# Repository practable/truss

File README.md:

# truss

## Introduction

The truss remote laboratory has been designed for use with Structural Engineering and Engineering Design courses at the University of Edinburgh. The truss consists of 6 members, each with a full-bridge strain gauge arrangement using two biaxial strain gauges ([Kyowa KFGS-2-120-D16-11](./hw/docs/)). Strain gauge voltages are converted to digital signals using the [HX711 ADC](./hw/docs/) and this [HX711 library](https://www.arduino.cc/reference/en/libraries/hx711-arduino-library/) is used to read and tare the gauges. The truss is loaded using a [linear servo](./hw/docs/). 

## Contents

- [Firmware ./fw](./fw/)
- [Hardware ./hw](./hw/)
- [SBC ./sbc](./sbc/)
- [UI ./ui](./ui/)

## UI

User Interfaces have been designed with Vue3.js and built with Vite. There are currently three distinct versions of the UI that are built for production:

- default: all data and components available on the user interface.
- no-force: force data is hidden for student calculation from strain data.
- open-day: simplified control interface for demonstrations.

See [here](./ui/README.md) for details of the differences.

## Changing control interface on UI

The differences in the above UI versions amount to very simple changes in the Vue files. 

The load force can be controlled with either a slider or simple buttons (as well experimental versions of a skeuomorphic display and gamepad control). Simply update the `loadControlVersion` parameter in `App.vue`.

```
loadControlVersion: 1,    //0 => input field, 1=> slider, 2=>simulation of physical knob, 3 => direct commands typed, 4 => GamePad, 5 => open day, simple buttons
```

To change whether the load force is displayed or the theoretical strains are available, update the boolean parameters in `src/modules/uiStore.js`:

```
show_force: false,       //should force values be displayed on the UI
show_theory: false,      //should the theoretical values component be available on the UI
```

## Firmware

The truss remote lab has been designed around the Arduino Nano 33 IoT. The firmware uses a state machine with 11 states, including reading, writing, taring and resetting strain gauges and moving the linear actuator. A single microcontroller performs both reading and writing of data. The state machine will remain in the READ state until a user command to change state. Upon performing that state the state machine will return to READ. The required libraries are included [here](./fw/libraries/). 

The firmware sends and receives JSON messages, eg:

Mode control, received from UI through Serial (for all commands see [SerialCommands](./fw/MiniTruss/):

```
{"set": "position", "to": value} 
{"set": "mode", "to": "move"} 
{"set": "mode", "to":"tare_all"} 
```

Sending data to UI through Serial:
```
{"load_cell":"20.0", "gauge_1": "100.0", "gauge_2": "100.0", "gauge_3": "100.0", "gauge_4": "100.0", "gauge_5": "100.0", "gauge_6": "100.0", "state":"1", "pos":"10"}
```

## PCB

The PCB requires a 12V input and provides output voltages for different components: 10V (load cell excitation voltage), 6V (linear actuator power) and 5V (strain gauge excitation voltage). Details of jumper requirements for setting up the PCB in different modes will be added (TODO).

## Hardware

The [Actuonix L16](./hw/docs/Actuonix+L16+Datasheet.pdf) linear actuator uses the custom library LinearServo for setting its position. It has a 50mm stroke length, but is limited in this remote lab to a maximum of 20% extension (providing around 150N of load on the truss).

## Re-calibration procedure

If a strain gauge value no longer reads an acceptable result (within your experimental tolerance) then the scale factor needs to be updated in the firmware.

- Note the value in micro-strain that the gauge is currently reading (current_value)
- Note the current scale factor for that gauge (current_factor)
- Calculate the value that you want it to read based on the load force (new_value)
- new_factor = current_value*current_factor / new_value

Using the debug UI (or any other means of sending a JSON command through Websocket to the experiment): send the new calibration data:

```
{"set":"cal","to":[2.0,2.1,2.2,2.3,2.4,2.5,2.6],"auth":"foo"}
```

Using the auth code that you set up initially.

Then reset to the STARTUP state so that the firmware loads the new calibration data:

```
{"set":"state","to":"STATE_STARTUP"}
```

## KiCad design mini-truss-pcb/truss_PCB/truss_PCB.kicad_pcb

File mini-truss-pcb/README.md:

## Mini Truss PCB design

# Current state

An Arduino Nano 33 IoT is used as the microcontroller for the lab. Firmware, in an unfinished state, is available [here](https://github.com/dpreid/truss-firmware/tree/main/MiniTruss). The latest mini-truss firmware is available on the develop branch.

The PCB design currently consists of the analogue-to-digital converters (ADC) for strain gauge measurements and the Arduino Nano 33 IoT. The ADC uses the [HX711](https://github.com/dpreid/mini-truss-pcb/blob/main/docs/hx711_english.pdf)

Firmware and PCB updates for the new [linear actuator](https://github.com/dpreid/mini-truss-pcb/blob/main/docs/Actuonix%2BL16%2BDatasheet.pdf) have been incorporated into the latest version.

# TODO

- Check correct resistance values are being used for voltage divider within ADC unit (R1 and R2 and then equivalents).
- TBC, whether we will stick with the Arduino Nano 33 IoT or convert to using Tim Drysdale's custom [microcontroller board](https://github.com/timdrysdale/atmega-demo). Perhaps better to use Arduino Nano (ie not 33 IoT) or Uno in order to have 5V pins and not require a logic level shifter.
- testing with prototype mini truss once strain gauges are ordered.

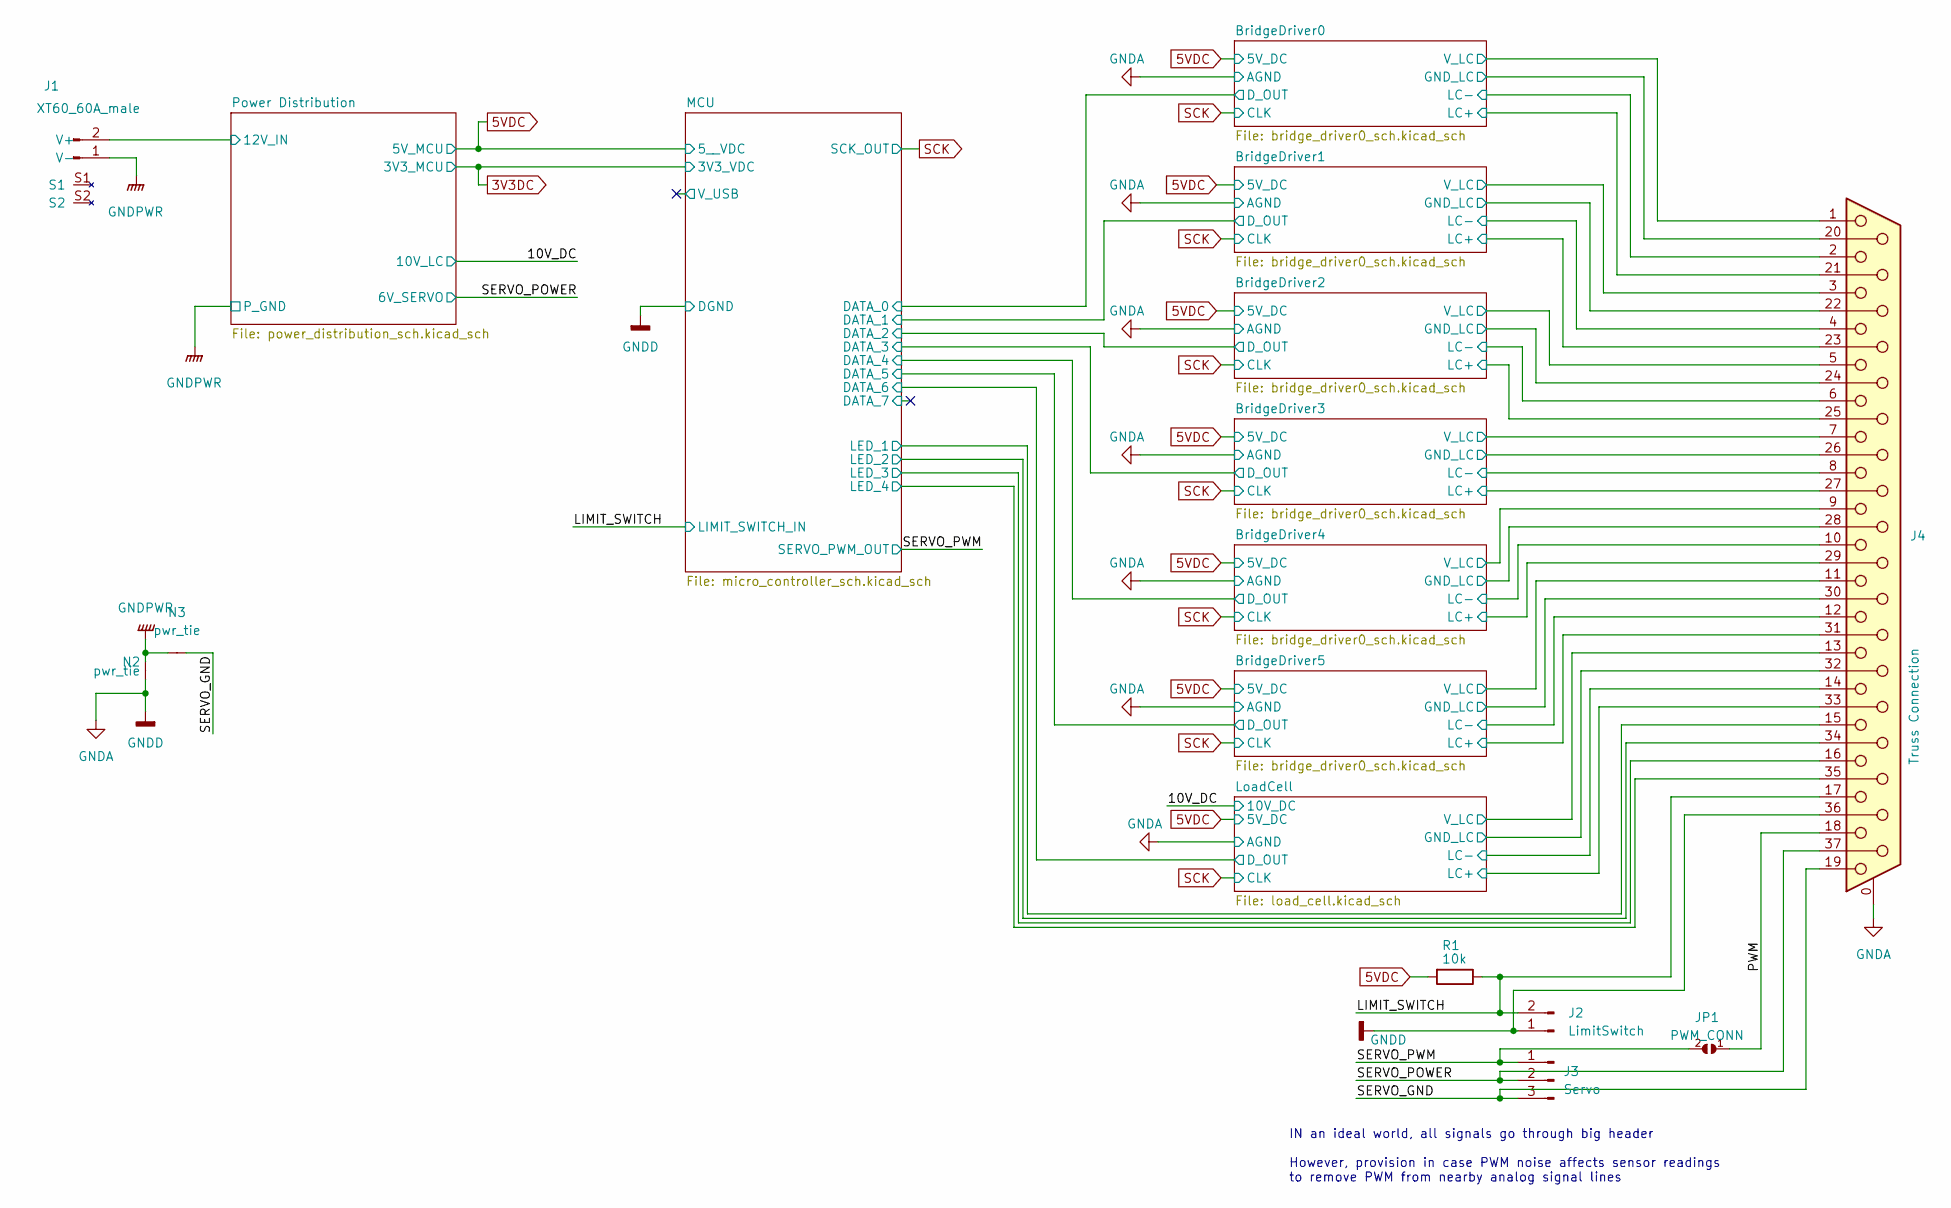
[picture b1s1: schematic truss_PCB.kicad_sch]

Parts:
J1: XT60_60A_male; AMASS_XT60PW-M
J2: LimitSwitch; Molex_KK-254_AE-6410-02A_1x02_P2.54mm_Vertical
J3: Servo; PinHeader_1x03_P2.54mm_Vertical
J4: Truss Connection; DSUB-37_Female_Vertical_P2.77x2.84mm_MountingHoles
JP1: PWM_CONN; SolderJumper-2_P1.3mm_Open_RoundedPad1.0x1.5mm
N2, N3: pwr_tie; NetTie-8-15A_1oz_2oz
R1: 10k; R_0805_2012Metric_Pad1.20x1.40mm_HandSolder

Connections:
5VDC: R1.2; also elsewhere on the board
/BridgeDriver0/LC+: J4.21; also elsewhere on the board
/BridgeDriver0/LC-: J4.2; also elsewhere on the board
/BridgeDriver0/V_LC: J4.1; also elsewhere on the board
/BridgeDriver1/LC+: J4.23; also elsewhere on the board
/BridgeDriver1/LC-: J4.4; also elsewhere on the board
/BridgeDriver1/V_LC: J4.3; also elsewhere on the board
/BridgeDriver2/LC+: J4.25; also elsewhere on the board
/BridgeDriver2/LC-: J4.6; also elsewhere on the board
/BridgeDriver2/V_LC: J4.5; also elsewhere on the board
/BridgeDriver3/LC+: J4.27; also elsewhere on the board
/BridgeDriver3/LC-: J4.8; also elsewhere on the board
/BridgeDriver3/V_LC: J4.7; also elsewhere on the board
/BridgeDriver4/LC+: J4.29; also elsewhere on the board
/BridgeDriver4/LC-: J4.10; also elsewhere on the board
/BridgeDriver4/V_LC: J4.9; also elsewhere on the board
/BridgeDriver5/LC+: J4.31; also elsewhere on the board
/BridgeDriver5/LC-: J4.12; also elsewhere on the board
/BridgeDriver5/V_LC: J4.11; also elsewhere on the board
/LIMIT_SWITCH: J2.2, J4.17, R1.1; also elsewhere on the board
/LoadCell/LC+: J4.33; also elsewhere on the board
/LoadCell/LC-: J4.14; also elsewhere on the board
/LoadCell/V_LC: J4.13; also elsewhere on the board
/MCU/LED_2: J4.34; also elsewhere on the board
/MCU/LED_3: J4.16; also elsewhere on the board
/MCU/LED_4: J4.35; also elsewhere on the board
/MCU/SPARE_0: J4.15; also elsewhere on the board
/PWM: J4.18, JP1.1 (A)
/Power Distribution/12V_IN: J1.2 (V+); also elsewhere on the board
/SERVO_GND: J3.3, J4.19, N3.2 (C)
/SERVO_POWER: J3.2, J4.37; also elsewhere on the board
/SERVO_PWM: J3.1, JP1.2 (B); also elsewhere on the board
GNDA: J2.1, J4.0 (PAD), J4.20, J4.22, J4.24, J4.26, J4.28, J4.30, J4.32, J4.36, N2.1 (A); also elsewhere on the board
GNDPWR: J1.1 (V-), N2.2 (C), N3.1 (A); also elsewhere on the board

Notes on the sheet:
IN an ideal world, all signals go through big header However, provision in case PWM noise affects sensor readings to remove PWM from nearby analog signal lines

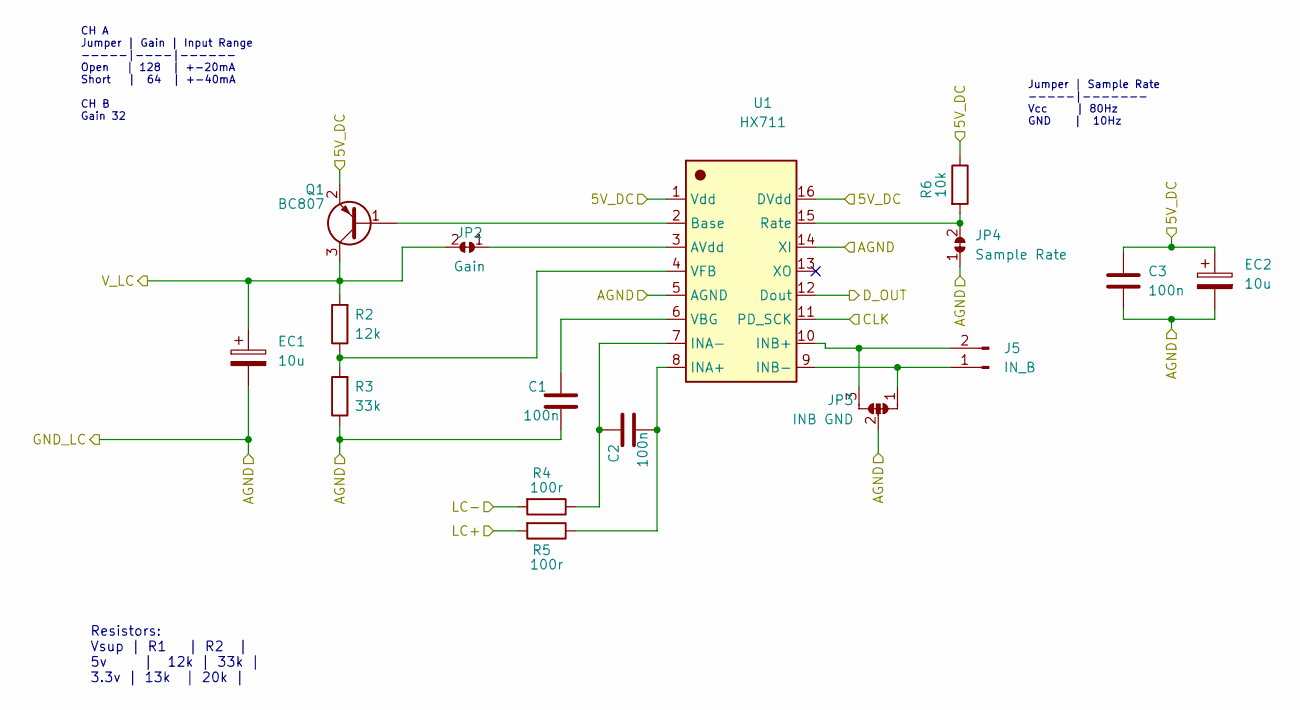
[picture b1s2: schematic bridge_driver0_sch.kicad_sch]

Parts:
C1, C2, C3: 100n; C_0805_2012Metric_Pad1.18x1.45mm_HandSolder
EC1, EC2: 10u; CP_Elec_6.3x5.9
J5: IN_B; PinHeader_1x02_P1.27mm_Vertical
JP2: Gain; SolderJumper-2_P1.3mm_Bridged_RoundedPad1.0x1.5mm
JP3: INB GND; SolderJumper-3_P1.3mm_Bridged12_RoundedPad1.0x1.5mm_DoubleJ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
JP4: Sample Rate; SolderJumper-2_P1.3mm_Bridged_RoundedPad1.0x1.5mm
Q1: BC807; SOT-23
R2: 12k; R_0805_2012Metric_Pad1.20x1.40mm_HandSolder
R3: 33k; R_0805_2012Metric_Pad1.20x1.40mm_HandSolder
R4, R5: 100r; R_0805_2012Metric_Pad1.20x1.40mm_HandSolder
R6: 10k; R_0805_2012Metric_Pad1.20x1.40mm_HandSolder
U1: HX711; SOP-16_4.55x10.3mm_P1.27mm

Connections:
5VDC: C3.1, EC2.1, Q1.2 (E), R6.1, U1.1 (Vdd), U1.16 (DVdd); also elsewhere on the board
/BridgeDriver0/D_OUT: U1.12 (Dout); also elsewhere on the board
/BridgeDriver0/LC+: R5.2; also elsewhere on the board
/BridgeDriver0/LC-: R4.2; also elsewhere on the board
/BridgeDriver0/V_LC: EC1.1, JP2.2 (B), Q1.3 (C), R2.2; also elsewhere on the board
GNDA: C1.2, C3.2, EC1.2, EC2.2, JP3.2 (C), JP4.1 (A), R3.1, U1.5 (AGND), U1.14 (XI); also elsewhere on the board
unnamed: C1.1, U1.6 (VBG)
unnamed: C2.1, R4.1, U1.7 (INA-)
unnamed: C2.2, R5.1, U1.8 (INA+)
unnamed: J5.1, JP3.1 (A), U1.9 (INB-)
unnamed: J5.2, JP3.3 (B), U1.10 (INB+)
unnamed: JP2.1 (A), U1.3 (AVdd)
unnamed: JP4.2 (B), R6.2, U1.15 (Rate)
unnamed: Q1.1 (B), U1.2 (Base)
unnamed: R2.1, R3.2, U1.4 (VFB)
SCK: U1.11 (PD_SCK); also elsewhere on the board

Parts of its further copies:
C4, C5, C6, C7, C8, C9, C10, C11, C12, C13, C14, C15, C16, C17, C18: 100n; C_0805_2012Metric_Pad1.18x1.45mm_HandSolder
EC3, EC4, EC5, EC6, EC7, EC8, EC9, EC10, EC11, EC12: 10u; CP_Elec_6.3x5.9
J6, J7, J8, J9, J10: IN_B; PinHeader_1x02_P1.27mm_Vertical
JP5, JP8, JP11, JP14, JP17: Gain; SolderJumper-2_P1.3mm_Bridged_RoundedPad1.0x1.5mm
JP6, JP9, JP12, JP15, JP18: INB GND; SolderJumper-3_P1.3mm_Bridged12_RoundedPad1.0x1.5mm_DoubleJ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
JP7, JP10, JP13, JP16, JP19: Sample Rate; SolderJumper-2_P1.3mm_Bridged_RoundedPad1.0x1.5mm
Q2, Q3, Q4, Q5, Q6: BC807; SOT-23
R7, R12, R17, R22, R27: 12k; R_0805_2012Metric_Pad1.20x1.40mm_HandSolder
R8, R13, R18, R23, R28: 33k; R_0805_2012Metric_Pad1.20x1.40mm_HandSolder
R9, R10, R14, R15, R19, R20, R24, R25, R29, R30: 100r; R_0805_2012Metric_Pad1.20x1.40mm_HandSolder
R11, R16, R21, R26, R31: 10k; R_0805_2012Metric_Pad1.20x1.40mm_HandSolder
U2, U3, U4, U5, U6: HX711; SOP-16_4.55x10.3mm_P1.27mm

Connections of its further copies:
5VDC: C6.1, C9.1, C12.1, C15.1, C18.1, EC4.1, EC6.1, EC8.1, EC10.1, EC12.1, Q2.2 (E), Q3.2 (E), Q4.2 (E), Q5.2 (E), Q6.2 (E), R11.1, R16.1, R21.1, R26.1, R31.1, U2.1 (Vdd), U2.16 (DVdd), U3.1 (Vdd), U3.16 (DVdd), U4.1 (Vdd), U4.16 (DVdd), U5.1 (Vdd), U5.16 (DVdd), U6.1 (Vdd), U6.16 (DVdd); also elsewhere on the board
/BridgeDriver1/D_OUT: U2.12 (Dout); also elsewhere on the board
/BridgeDriver1/LC+: R10.2; also elsewhere on the board
/BridgeDriver1/LC-: R9.2; also elsewhere on the board
/BridgeDriver1/V_LC: EC3.1, JP5.2 (B), Q2.3 (C), R7.2; also elsewhere on the board
/BridgeDriver2/D_OUT: U3.12 (Dout); also elsewhere on the board
/BridgeDriver2/LC+: R15.2; also elsewhere on the board
/BridgeDriver2/LC-: R14.2; also elsewhere on the board
/BridgeDriver2/V_LC: EC5.1, JP8.2 (B), Q3.3 (C), R12.2; also elsewhere on the board
/BridgeDriver3/D_OUT: U4.12 (Dout); also elsewhere on the board
/BridgeDriver3/LC+: R20.2; also elsewhere on the board
/BridgeDriver3/LC-: R19.2; also elsewhere on the board
/BridgeDriver3/V_LC: EC7.1, JP11.2 (B), Q4.3 (C), R17.2; also elsewhere on the board
/BridgeDriver4/D_OUT: U5.12 (Dout); also elsewhere on the board
/BridgeDriver4/LC+: R25.2; also elsewhere on the board
/BridgeDriver4/LC-: R24.2; also elsewhere on the board
/BridgeDriver4/V_LC: EC9.1, JP14.2 (B), Q5.3 (C), R22.2; also elsewhere on the board
/BridgeDriver5/D_OUT: U6.12 (Dout); also elsewhere on the board
/BridgeDriver5/LC+: R30.2; also elsewhere on the board
/BridgeDriver5/LC-: R29.2; also elsewhere on the board
/BridgeDriver5/V_LC: EC11.1, JP17.2 (B), Q6.3 (C), R27.2; also elsewhere on the board
GNDA: C4.2, C6.2, C7.2, C9.2, C10.2, C12.2, C13.2, C15.2, C16.2, C18.2, EC3.2, EC4.2, EC5.2, EC6.2, EC7.2, EC8.2, EC9.2, EC10.2, EC11.2, EC12.2, JP6.2 (C), JP7.1 (A), JP9.2 (C), JP10.1 (A), JP12.2 (C), JP13.1 (A), JP15.2 (C), JP16.1 (A), JP18.2 (C), JP19.1 (A), R8.1, R13.1, R18.1, R23.1, R28.1, U2.5 (AGND), U2.14 (XI), U3.5 (AGND), U3.14 (XI), U4.5 (AGND), U4.14 (XI), U5.5 (AGND), U5.14 (XI), U6.5 (AGND), U6.14 (XI); also elsewhere on the board
unnamed: C4.1, U2.6 (VBG)
unnamed: C5.1, R9.1, U2.7 (INA-)
unnamed: C5.2, R10.1, U2.8 (INA+)
unnamed: C7.1, U3.6 (VBG)
unnamed: C8.1, R14.1, U3.7 (INA-)
unnamed: C8.2, R15.1, U3.8 (INA+)
unnamed: C10.1, U4.6 (VBG)
unnamed: C11.1, R19.1, U4.7 (INA-)
unnamed: C11.2, R20.1, U4.8 (INA+)
unnamed: C13.1, U5.6 (VBG)
unnamed: C14.1, R24.1, U5.7 (INA-)
unnamed: C14.2, R25.1, U5.8 (INA+)
unnamed: C16.1, U6.6 (VBG)
unnamed: C17.1, R29.1, U6.7 (INA-)
unnamed: C17.2, R30.1, U6.8 (INA+)
unnamed: J6.1, JP6.1 (A), U2.9 (INB-)
unnamed: J6.2, JP6.3 (B), U2.10 (INB+)
unnamed: J7.1, JP9.1 (A), U3.9 (INB-)
unnamed: J7.2, JP9.3 (B), U3.10 (INB+)
unnamed: J8.1, JP12.1 (A), U4.9 (INB-)
unnamed: J8.2, JP12.3 (B), U4.10 (INB+)
unnamed: J9.1, JP15.1 (A), U5.9 (INB-)
unnamed: J9.2, JP15.3 (B), U5.10 (INB+)
unnamed: J10.1, JP18.1 (A), U6.9 (INB-)
unnamed: J10.2, JP18.3 (B), U6.10 (INB+)
unnamed: JP5.1 (A), U2.3 (AVdd)
unnamed: JP7.2 (B), R11.2, U2.15 (Rate)
unnamed: JP8.1 (A), U3.3 (AVdd)
unnamed: JP10.2 (B), R16.2, U3.15 (Rate)
unnamed: JP11.1 (A), U4.3 (AVdd)
unnamed: JP13.2 (B), R21.2, U4.15 (Rate)
unnamed: JP14.1 (A), U5.3 (AVdd)
unnamed: JP16.2 (B), R26.2, U5.15 (Rate)
unnamed: JP17.1 (A), U6.3 (AVdd)
unnamed: JP19.2 (B), R31.2, U6.15 (Rate)
unnamed: Q2.1 (B), U2.2 (Base)
unnamed: Q3.1 (B), U3.2 (Base)
unnamed: Q4.1 (B), U4.2 (Base)
unnamed: Q5.1 (B), U5.2 (Base)
unnamed: Q6.1 (B), U6.2 (Base)
unnamed: R7.1, R8.2, U2.4 (VFB)
unnamed: R12.1, R13.2, U3.4 (VFB)
unnamed: R17.1, R18.2, U4.4 (VFB)
unnamed: R22.1, R23.2, U5.4 (VFB)
unnamed: R27.1, R28.2, U6.4 (VFB)
SCK: U2.11 (PD_SCK), U3.11 (PD_SCK), U4.11 (PD_SCK), U5.11 (PD_SCK), U6.11 (PD_SCK); also elsewhere on the board

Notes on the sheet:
CH A Jumper | Gain | Input Range -----|----|------ Open | 128 | +-20mA Short | 64 | +-40mA CH B Gain 32
Resistors: Vsup | R1 | R2 | 5v | 12k | 33k | 3.3v | 13k | 20k |
Jumper | Sample Rate -----|------- Vcc | 80Hz GND | 10Hz

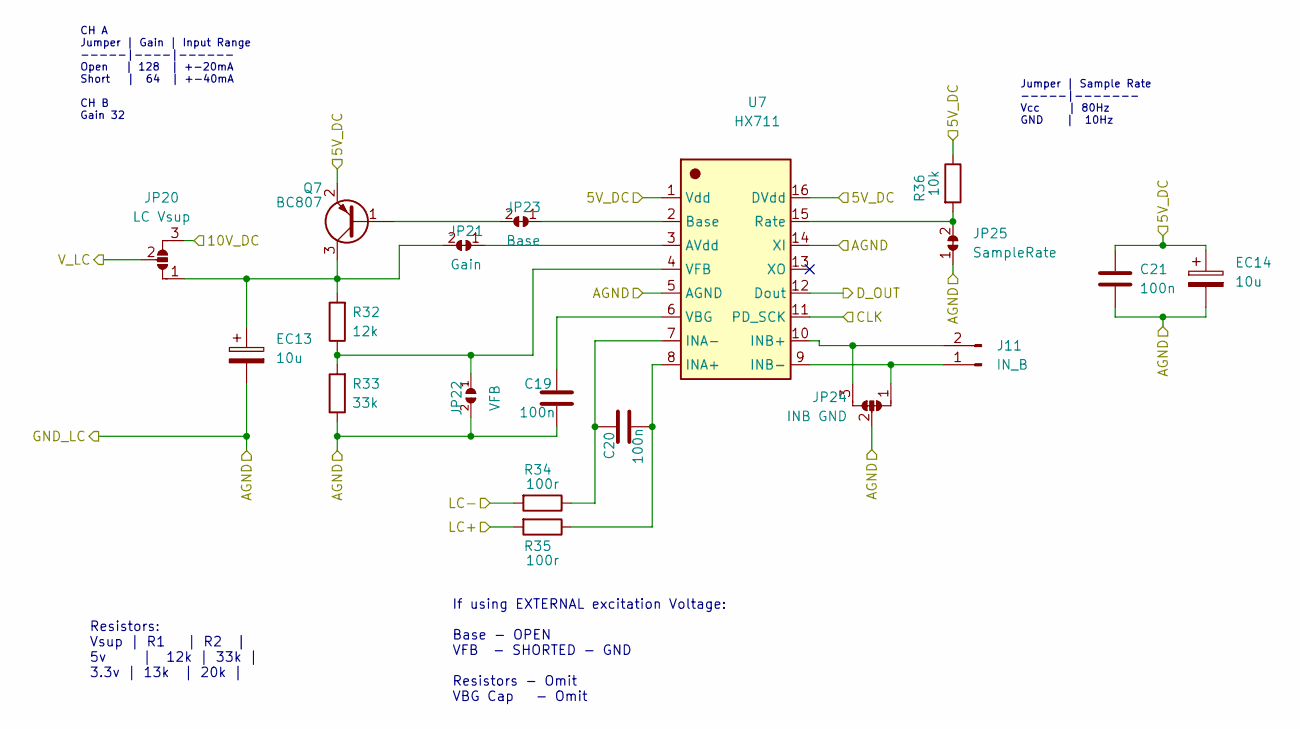
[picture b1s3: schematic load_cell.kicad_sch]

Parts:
C19, C20, C21: 100n; C_0805_2012Metric_Pad1.18x1.45mm_HandSolder
EC13, EC14: 10u; CP_Elec_6.3x5.9
J11: IN_B; PinHeader_1x02_P1.27mm_Vertical
JP20: LC Vsup; SolderJumper-3_P1.3mm_Open_RoundedPad1.0x1.5mm_NumberLabels
JP21: Gain; SolderJumper-2_P1.3mm_Bridged_RoundedPad1.0x1.5mm
JP22: VFB; SolderJumper-2_P1.3mm_Open_RoundedPad1.0x1.5mm
JP23: Base; SolderJumper-2_P1.3mm_Bridged_RoundedPad1.0x1.5mm
JP24: INB GND; SolderJumper-3_P1.3mm_Bridged12_RoundedPad1.0x1.5mm_DoubleJ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
JP25: SampleRate; SolderJumper-2_P1.3mm_Bridged_RoundedPad1.0x1.5mm
Q7: BC807; SOT-23
R32: 12k; R_0805_2012Metric_Pad1.20x1.40mm_HandSolder
R33: 33k; R_0805_2012Metric_Pad1.20x1.40mm_HandSolder
R34, R35: 100r; R_0805_2012Metric_Pad1.20x1.40mm_HandSolder
R36: 10k; R_0805_2012Metric_Pad1.20x1.40mm_HandSolder
U7: HX711; SOP-16_4.55x10.3mm_P1.27mm

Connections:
5VDC: C21.1, EC14.1, Q7.2 (E), R36.1, U7.1 (Vdd), U7.16 (DVdd); also elsewhere on the board
/10V_DC: JP20.3 (B); also elsewhere on the board
/LoadCell/D_OUT: U7.12 (Dout); also elsewhere on the board
/LoadCell/LC+: R35.2; also elsewhere on the board
/LoadCell/LC-: R34.2; also elsewhere on the board
/LoadCell/V_LC: JP20.2 (C); also elsewhere on the board
GNDA: C19.2, C21.2, EC13.2, EC14.2, JP22.2 (B), JP24.2 (C), JP25.1 (A), R33.1, U7.5 (AGND), U7.14 (XI); also elsewhere on the board
unnamed: C19.1, U7.6 (VBG)
unnamed: C20.1, R34.1, U7.7 (INA-)
unnamed: C20.2, R35.1, U7.8 (INA+)
unnamed: EC13.1, JP20.1 (A), JP21.2 (B), Q7.3 (C), R32.2
unnamed: J11.1, JP24.1 (A), U7.9 (INB-)
unnamed: J11.2, JP24.3 (B), U7.10 (INB+)
unnamed: JP21.1 (A), U7.3 (AVdd)
unnamed: JP22.1 (A), R32.1, R33.2, U7.4 (VFB)
unnamed: JP23.1 (A), U7.2 (Base)
unnamed: JP23.2 (B), Q7.1 (B)
unnamed: JP25.2 (B), R36.2, U7.15 (Rate)
SCK: U7.11 (PD_SCK); also elsewhere on the board

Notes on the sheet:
If using EXTERNAL excitation Voltage: Base - OPEN VFB - SHORTED - GND Resistors - Omit VBG Cap - Omit
Jumper | Sample Rate -----|------- Vcc | 80Hz GND | 10Hz
CH A Jumper | Gain | Input Range -----|----|------ Open | 128 | +-20mA Short | 64 | +-40mA CH B Gain 32
Resistors: Vsup | R1 | R2 | 5v | 12k | 33k | 3.3v | 13k | 20k |

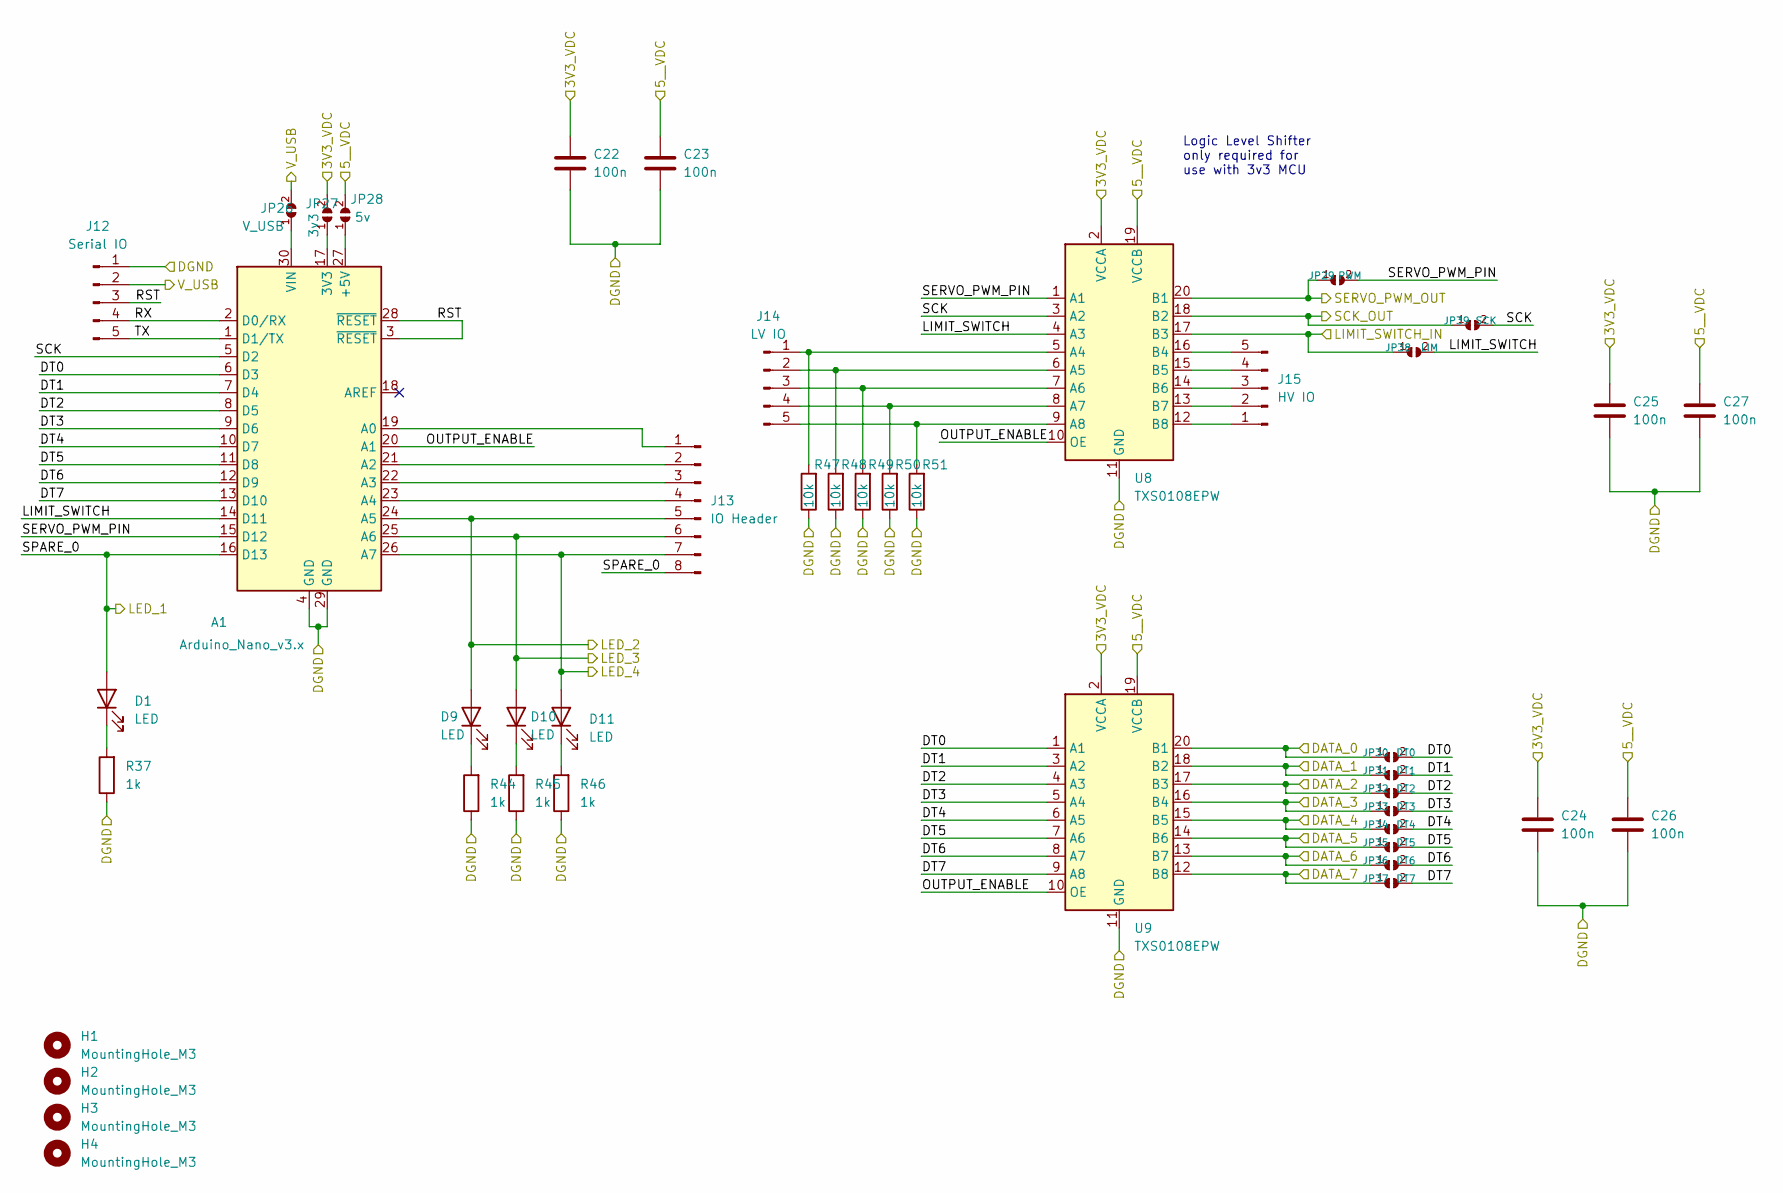
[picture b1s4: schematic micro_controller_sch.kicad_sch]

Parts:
A1: Arduino_Nano_v3.x; Arduino_Nano
C22, C23, C24, C25, C26, C27: 100n; C_0805_2012Metric_Pad1.18x1.45mm_HandSolder
D1, D9, D10, D11: LED; D_0805_2012Metric_Pad1.15x1.40mm_HandSolder
H1, H2, H3, H4: MountingHole_M3; MountingHole_3.2mm_M3_Pad_Via
J12: Serial IO; PinHeader_1x05_P2.54mm_Vertical
J13: IO Header; PinHeader_1x08_P2.54mm_Vertical
J14: LV IO; PinHeader_1x05_P2.54mm_Vertical
J15: HV IO; PinHeader_1x05_P2.54mm_Vertical
JP26: V_USB; SolderJumper-2_P1.3mm_Open_RoundedPad1.0x1.5mm
JP27: 3v3; SolderJumper-2_P1.3mm_Open_RoundedPad1.0x1.5mm
JP28: 5v; SolderJumper-2_P1.3mm_Open_RoundedPad1.0x1.5mm
JP29: PWM; SolderJumper-2_P1.3mm_Open_RoundedPad1.0x1.5mm
JP30: DT0; SolderJumper-2_P1.3mm_Open_RoundedPad1.0x1.5mm
JP31: DT1; SolderJumper-2_P1.3mm_Open_RoundedPad1.0x1.5mm
JP32: DT2; SolderJumper-2_P1.3mm_Open_RoundedPad1.0x1.5mm
JP33: DT3; SolderJumper-2_P1.3mm_Open_RoundedPad1.0x1.5mm
JP34: DT4; SolderJumper-2_P1.3mm_Open_RoundedPad1.0x1.5mm
JP35: DT5; SolderJumper-2_P1.3mm_Open_RoundedPad1.0x1.5mm
JP36: DT6; SolderJumper-2_P1.3mm_Open_RoundedPad1.0x1.5mm
JP37: DT7; SolderJumper-2_P1.3mm_Open_RoundedPad1.0x1.5mm
JP38: LIM; SolderJumper-2_P1.3mm_Open_RoundedPad1.0x1.5mm
JP39: SCK; SolderJumper-2_P1.3mm_Open_RoundedPad1.0x1.5mm
R37, R44, R45, R46: 1k; R_0805_2012Metric_Pad1.20x1.40mm_HandSolder
R47, R48, R49, R50, R51: 10k; R_0805_2012Metric_Pad1.20x1.40mm_HandSolder
U8, U9: TXS0108EPW; TSSOP-20_4.4x6.5mm_P0.65mm

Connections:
3V3DC: C22.1, C24.1, C25.1, JP27.2 (B), U8.2 (VCCA), U9.2 (VCCA); also elsewhere on the board
5VDC: C23.1, C26.1, C27.1, JP28.2 (B), U8.19 (VCCB), U9.19 (VCCB); also elsewhere on the board
/BridgeDriver0/D_OUT: JP30.1 (A), U9.20 (B1); also elsewhere on the board
/BridgeDriver1/D_OUT: JP31.1 (A), U9.18 (B2); also elsewhere on the board
/BridgeDriver2/D_OUT: JP32.1 (A), U9.17 (B3); also elsewhere on the board
/BridgeDriver3/D_OUT: JP33.1 (A), U9.16 (B4); also elsewhere on the board
/BridgeDriver4/D_OUT: JP34.1 (A), U9.15 (B5); also elsewhere on the board
/BridgeDriver5/D_OUT: JP35.1 (A), U9.14 (B6); also elsewhere on the board
/LIMIT_SWITCH: JP38.1 (A), U8.17 (B3); also elsewhere on the board
/LoadCell/D_OUT: JP36.1 (A), U9.13 (B7); also elsewhere on the board
/MCU/DATA_7: JP37.1 (A), U9.12 (B8)
/MCU/DT0: A1.6 (D3), JP30.2 (B), U9.1 (A1)
/MCU/DT1: A1.7 (D4), JP31.2 (B), U9.3 (A2)
/MCU/DT2: A1.8 (D5), JP32.2 (B), U9.4 (A3)
/MCU/DT3: A1.9 (D6), JP33.2 (B), U9.5 (A4)
/MCU/DT4: A1.10 (D7), JP34.2 (B), U9.6 (A5)
/MCU/DT5: A1.11 (D8), JP35.2 (B), U9.7 (A6)
/MCU/DT6: A1.12 (D9), JP36.2 (B), U9.8 (A7)
/MCU/DT7: A1.13 (D10), JP37.2 (B), U9.9 (A8)
/MCU/LED_2: A1.24 (A5), D9.2 (A), J13.5; also elsewhere on the board
/MCU/LED_3: A1.25 (A6), D10.2 (A), J13.6; also elsewhere on the board
/MCU/LED_4: A1.26 (A7), D11.2 (A), J13.7; also elsewhere on the board
/MCU/LIMIT_SWITCH: A1.14 (D11), JP38.2 (B), U8.4 (A3)
/MCU/OUTPUT_ENABLE: A1.20 (A1), U8.10 (OE), U9.10 (OE)
/MCU/RST: A1.3 (~RESET), A1.28 (~RESET), J12.3
/MCU/RX: A1.2 (D0/RX), J12.4
/MCU/SCK: A1.5 (D2), JP39.2 (B), U8.3 (A2)
/MCU/SERVO_PWM_PIN: A1.15 (D12), JP29.2 (B), U8.1 (A1)
/MCU/SPARE_0: A1.16 (D13), D1.2 (A), J13.8; also elsewhere on the board
/MCU/TX: A1.1 (D1/TX), J12.5
/MCU/V_USB: J12.2, JP26.2 (B)
/SERVO_PWM: JP29.1 (A), U8.20 (B1); also elsewhere on the board
GNDA: A1.4 (GND), A1.29 (GND), C22.2, C23.2, C24.2, C25.2, C26.2, C27.2, J12.1, R37.1, R44.1, R45.1, R46.1, R47.1, R48.1, R49.1, R50.1, R51.1, U8.11 (GND), U9.11 (GND); also elsewhere on the board
unnamed: A1.17 (3V3), JP27.1 (A)
unnamed: A1.19 (A0), J13.1
unnamed: A1.21 (A2), J13.2
unnamed: A1.22 (A3), J13.3
unnamed: A1.23 (A4), J13.4
unnamed: A1.27 (+5V), JP28.1 (A)
unnamed: A1.30 (VIN), JP26.1 (A)
unnamed: D1.1 (K), R37.2
unnamed: D9.1 (K), R44.2
unnamed: D10.1 (K), R45.2
unnamed: D11.1 (K), R46.2
unnamed: J14.1, R47.2, U8.5 (A4)
unnamed: J14.2, R48.2, U8.6 (A5)
unnamed: J14.3, R49.2, U8.7 (A6)
unnamed: J14.4, R50.2, U8.8 (A7)
unnamed: J14.5, R51.2, U8.9 (A8)
unnamed: J15.1, U8.12 (B8)
unnamed: J15.2, U8.13 (B7)
unnamed: J15.3, U8.14 (B6)
unnamed: J15.4, U8.15 (B5)
unnamed: J15.5, U8.16 (B4)
SCK: JP39.1 (A), U8.18 (B2); also elsewhere on the board

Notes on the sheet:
Logic Level Shifter only required for use with 3v3 MCU

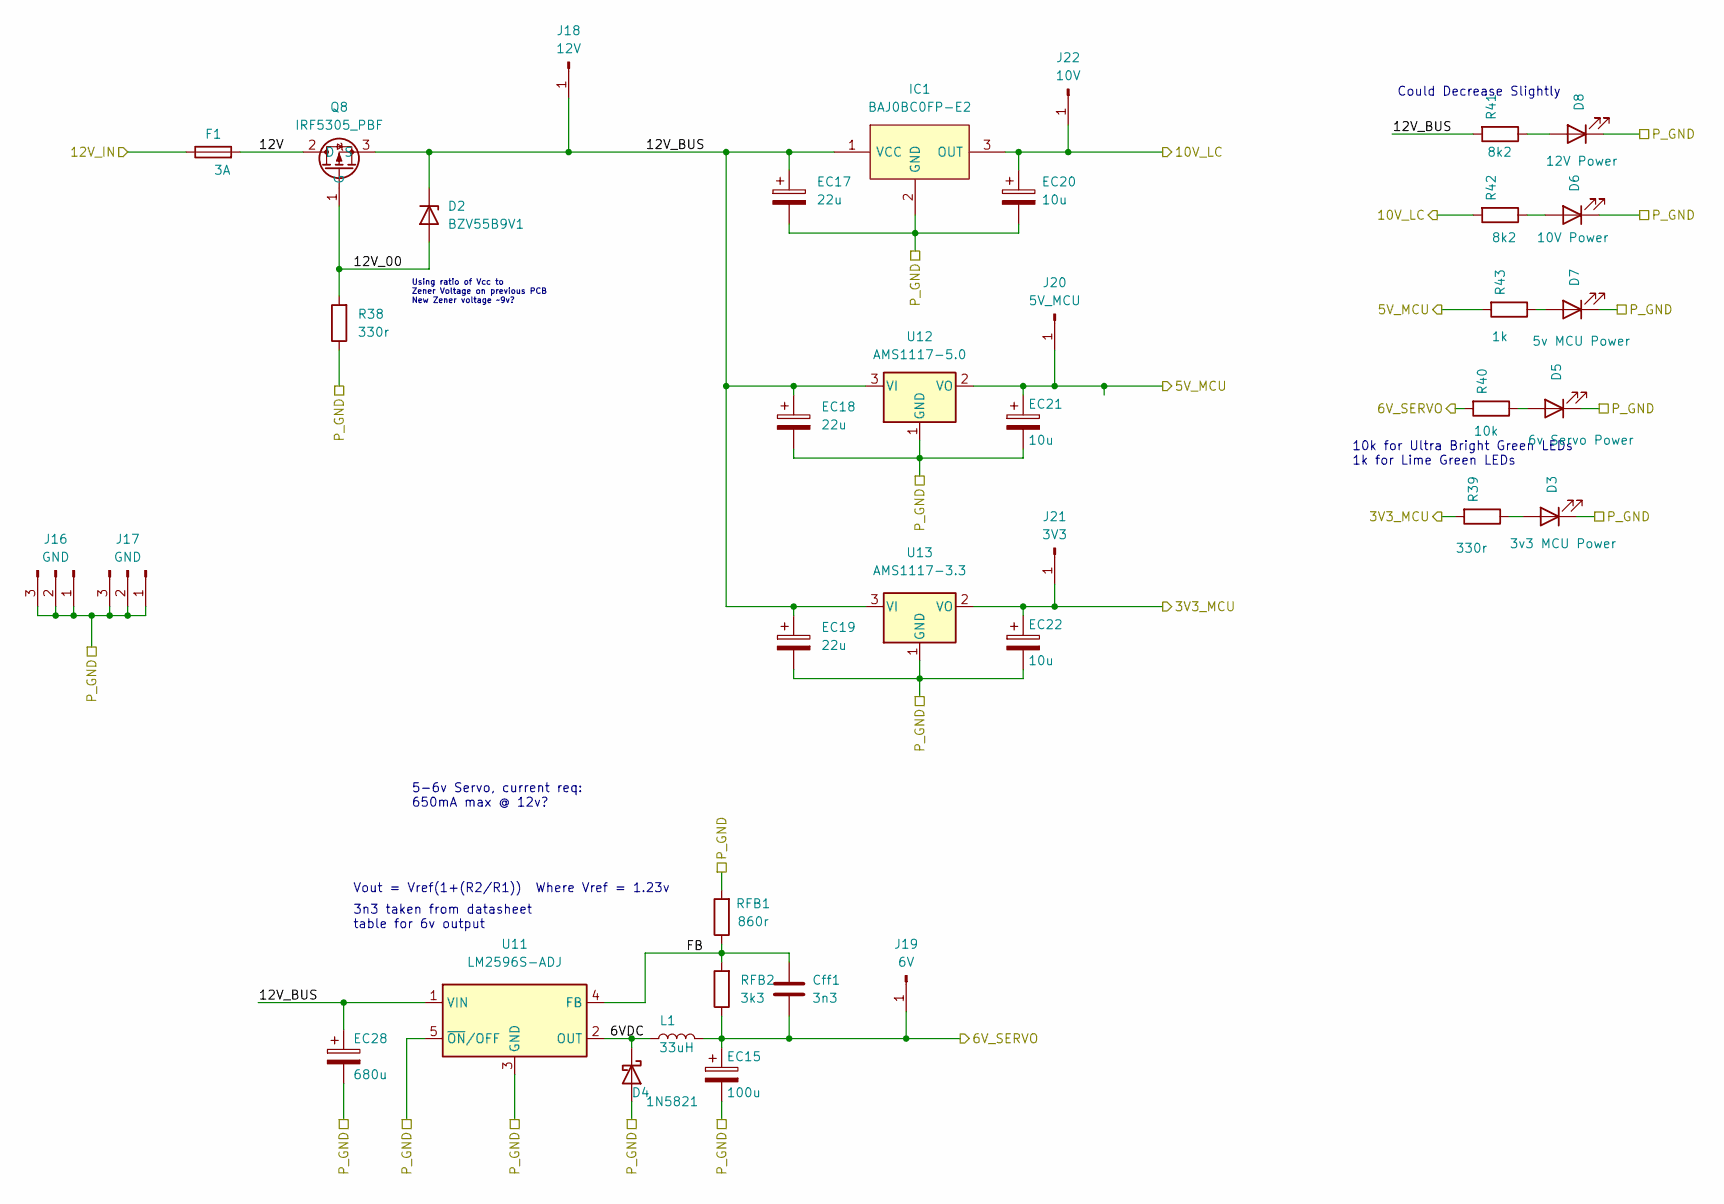
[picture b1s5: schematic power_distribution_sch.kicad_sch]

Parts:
Cff1: 3n3; C_0805_2012Metric_Pad1.18x1.45mm_HandSolder
D2: BZV55B9V1; D_MiniMELF
D3: 3v3 MCU Power; D_0805_2012Metric_Pad1.15x1.40mm_HandSolder
D4: 1N5821; D_SMA
D5: 6v Servo Power; D_0805_2012Metric_Pad1.15x1.40mm_HandSolder
D6: 10V Power; D_0805_2012Metric_Pad1.15x1.40mm_HandSolder
D7: 5v MCU Power; D_0805_2012Metric_Pad1.15x1.40mm_HandSolder
D8: 12V Power; D_0805_2012Metric_Pad1.15x1.40mm_HandSolder
EC15: 100u; CP_Elec_10x10
EC17, EC18, EC19: 22u; CP_Elec_6.3x5.9
EC20, EC21, EC22: 10u; CP_Elec_6.3x5.9
EC28: 680u; CP_Elec_10x10
F1: 3A; Fuseholder_Cylinder-5x20mm_Stelvio-Kontek_PTF78_Horizontal_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
IC1: BAJ0BC0FP-E2; TO-252-2; Manufacturer_Part_Number BAJ0BC0FP-E2
J16, J17: GND; PinHeader_1x03_P2.54mm_Vertical
J18: 12V; PinHeader_1x01_P2.54mm_Vertical
J19: 6V; PinHeader_1x01_P2.54mm_Vertical
J20: 5V_MCU; PinHeader_1x01_P2.54mm_Vertical
J21: 3V3; PinHeader_1x01_P2.54mm_Vertical
J22: 10V; PinHeader_1x01_P2.54mm_Vertical
L1: 33uH; L_12x12mm_H8mm
Q8: IRF5305_PBF; TO-220-3_Vertical
R38, R39: 330r; R_0805_2012Metric_Pad1.20x1.40mm_HandSolder
R40: 10k; R_0805_2012Metric_Pad1.20x1.40mm_HandSolder
R41, R42: 8k2; R_0805_2012Metric_Pad1.20x1.40mm_HandSolder
R43: 1k; R_0805_2012Metric_Pad1.20x1.40mm_HandSolder
RFB1: 860r; R_0805_2012Metric_Pad1.20x1.40mm_HandSolder
RFB2: 3k3; R_0805_2012Metric_Pad1.20x1.40mm_HandSolder
U11: LM2596S-ADJ; TO-263-5_TabPin3
U12: AMS1117-5.0; SOT-223-3_TabPin2
U13: AMS1117-3.3; SOT-223-3_TabPin2

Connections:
3V3DC: EC22.1, J21.1, R39.2, U13.2 (VO); also elsewhere on the board
5VDC: EC21.1, J20.1, R43.2, U12.2 (VO); also elsewhere on the board
/10V_DC: EC20.1, IC1.3 (OUT), J22.1, R42.2; also elsewhere on the board
/Power Distribution/6VDC: D4.1 (K), L1.1, U11.2 (OUT)
/Power Distribution/12V: F1.2, Q8.2 (D)
/Power Distribution/12V_00: D2.2 (A), Q8.1 (G), R38.2
/Power Distribution/12V_BUS: D2.1 (K), EC17.1, EC18.1, EC19.1, EC28.1, IC1.1 (VCC), J18.1, Q8.3 (S), R41.2, U11.1 (VIN), U12.3 (VI), U13.3 (VI)
/Power Distribution/12V_IN: F1.1; also elsewhere on the board
/Power Distribution/FB: Cff1.1, RFB1.1, RFB2.2, U11.4 (FB)
/SERVO_POWER: Cff1.2, EC15.1, J19.1, L1.2, R40.2, RFB2.1; also elsewhere on the board
GNDPWR: D3.1 (K), D4.2 (A), D5.1 (K), D6.1 (K), D7.1 (K), D8.1 (K), EC15.2, EC17.2, EC18.2, EC19.2, EC20.2, EC21.2, EC22.2, EC28.2, IC1.2 (GND), J16.1, J16.2, J16.3, J17.1, J17.2, J17.3, R38.1, RFB1.2, U11.3 (GND), U11.5 (~ON/OFF), U12.1 (GND), U13.1 (GND); also elsewhere on the board
unnamed: D3.2 (A), R39.1
unnamed: D5.2 (A), R40.1
unnamed: D6.2 (A), R42.1
unnamed: D7.2 (A), R43.1
unnamed: D8.2 (A), R41.1

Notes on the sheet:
3n3 taken from datasheet table for 6v output
10k for Ultra Bright Green LEDs 1k for Lime Green LEDs
5-6v Servo, current req: 650mA max @ 12v?
Could Decrease Slightly
Using ratio of Vcc to Zener Voltage on previous PCB New Zener voltage ~9v?
Vout = Vref(1+(R2/R1)) Where Vref = 1.23v
